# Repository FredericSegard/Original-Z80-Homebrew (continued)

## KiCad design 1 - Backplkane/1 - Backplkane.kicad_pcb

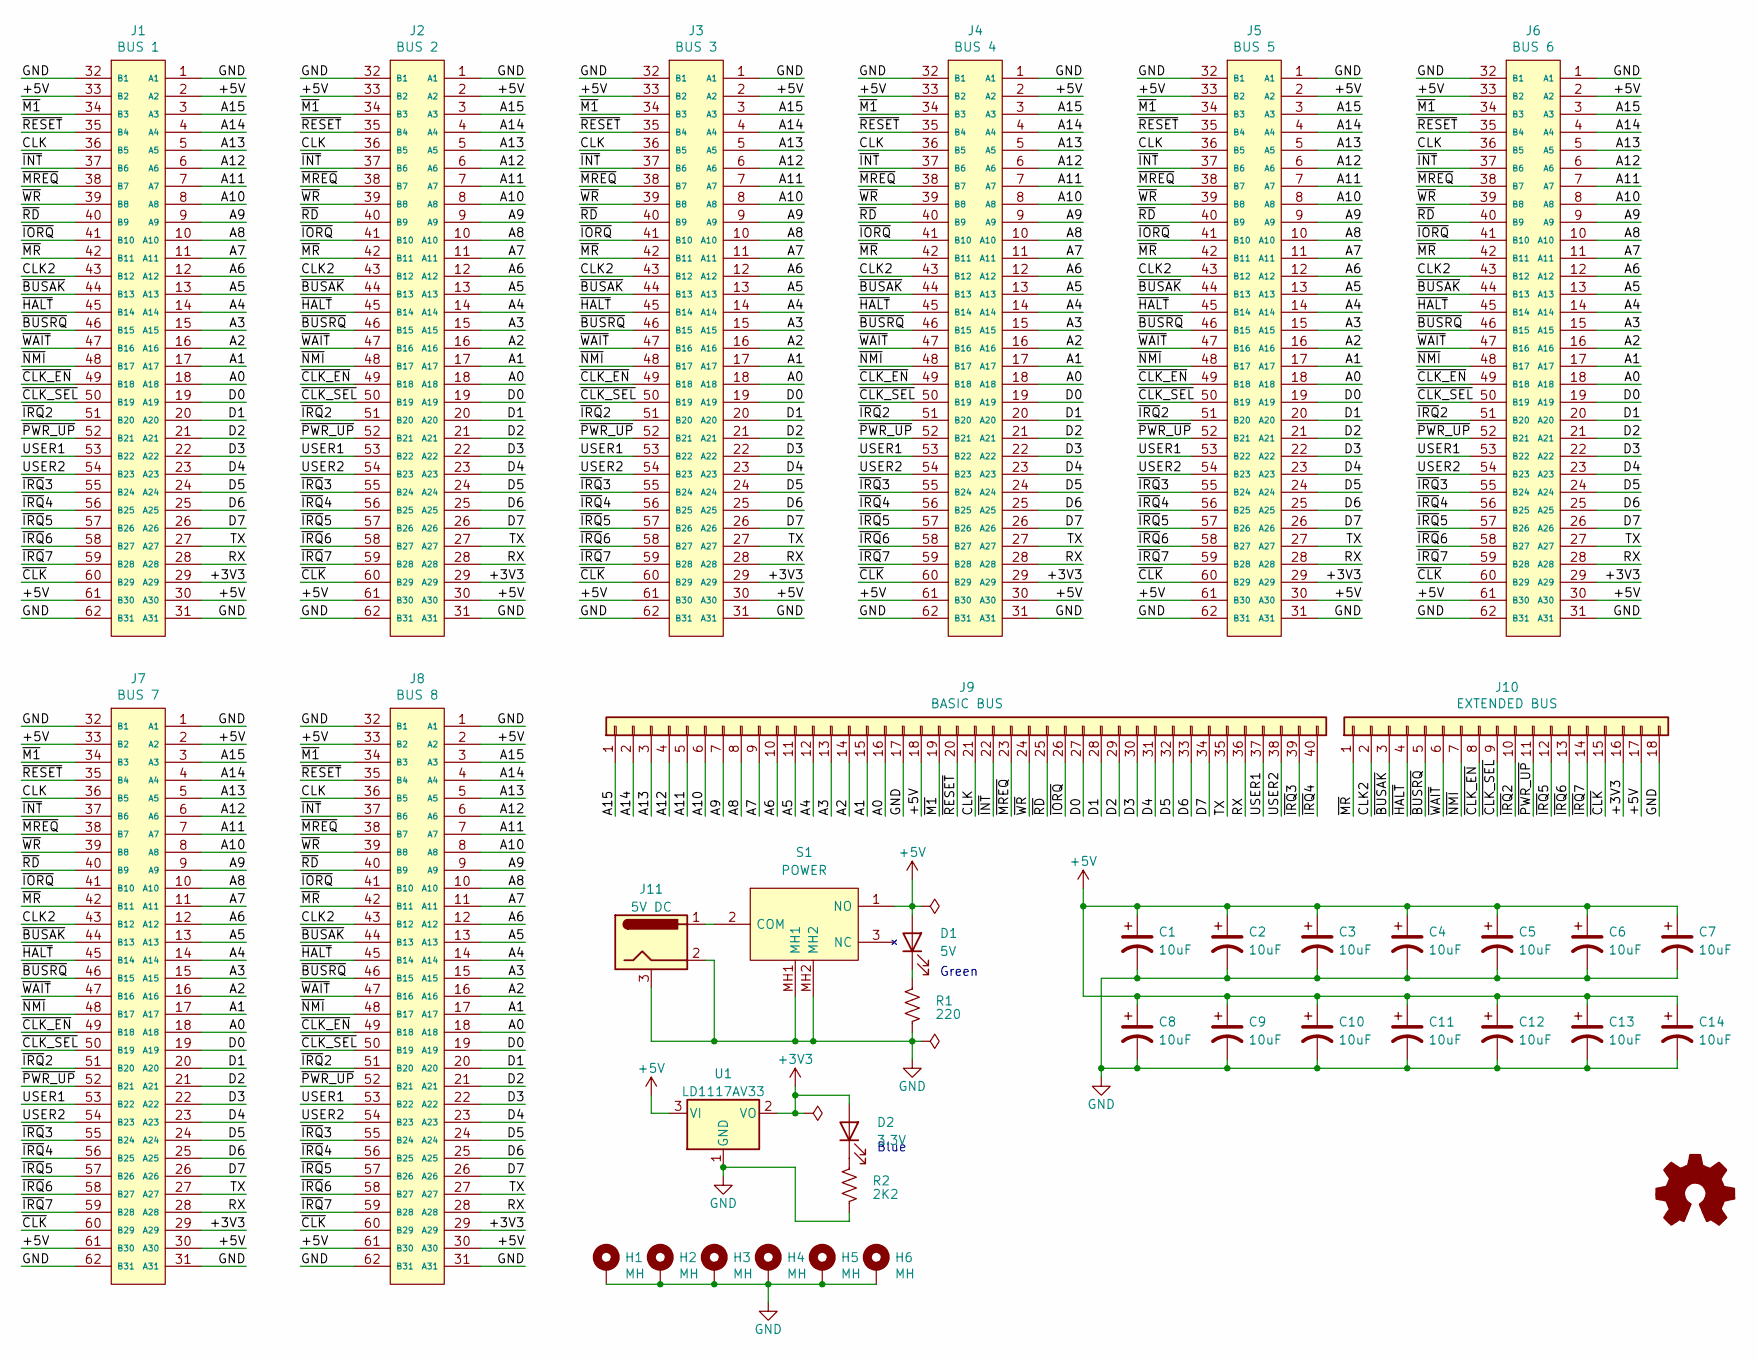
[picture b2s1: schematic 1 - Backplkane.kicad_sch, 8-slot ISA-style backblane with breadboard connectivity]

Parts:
C1, C2, C3, C4, C5, C6, C7, C8, C9, C10, C11, C12, C13, C14: 10uF; CP_Radial_D6.3mm_P2.50mm
D1: 5V; LED_D3.0mm
D2: 3.3V; LED_D3.0mm
H1, H2, H3, H4, H5, H6: MH; MountingHole_3.2mm_M3_Pad_Via
J1: BUS 1; ISA_Connector; Mouser Part Number 571-6-5530843-5
J2: BUS 2; ISA_Connector; Mouser Part Number 571-6-5530843-5
J3: BUS 3; ISA_Connector; Mouser Part Number 571-6-5530843-5
J4: BUS 4; ISA_Connector; Mouser Part Number 571-6-5530843-5
J5: BUS 5; ISA_Connector; Mouser Part Number 571-6-5530843-5
J6: BUS 6; ISA_Connector; Mouser Part Number 571-6-5530843-5
J7: BUS 7; ISA_Connector; Mouser Part Number 571-6-5530843-5
J8: BUS 8; ISA_Connector; Mouser Part Number 571-6-5530843-5
J9: BASIC BUS; PinHeader_1x40_P2.54mm_Vertical
J10: EXTENDED BUS; PinHeader_1x18_P2.54mm_Vertical
J11: 5V DC; BarrelJack_Horizontal
R1: 220; R_Axial_DIN0207_L6.3mm_D2.5mm_P10.16mm_Horizontal
R2: 2K2; R_Axial_DIN0207_L6.3mm_D2.5mm_P10.16mm_Horizontal
S1: POWER; SPDT_NKK_SWITCH_M2012S2A2W30; Manufacturer_Part_Number M2012S2A2W30; Mouser Part Number 633-M2012S2A2W30
U1: LD1117AV33; TO-126-3_Horizontal_TabDown

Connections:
+3V3: D2.2 (A), J1.29 (A29), J2.29 (A29), J3.29 (A29), J4.29 (A29), J5.29 (A29), J6.29 (A29), J7.29 (A29), J8.29 (A29), J10.16, U1.2 (VO)
+5V: C1.1, C2.1, C3.1, C4.1, C5.1, C6.1, C7.1, C8.1, C9.1, C10.1, C11.1, C12.1, C13.1, C14.1, D1.2 (A), J1.2 (A2), J1.30 (A30), J1.33 (B2), J1.61 (B30), J2.2 (A2), J2.30 (A30), J2.33 (B2), J2.61 (B30), J3.2 (A2), J3.30 (A30), J3.33 (B2), J3.61 (B30), J4.2 (A2), J4.30 (A30), J4.33 (B2), J4.61 (B30), J5.2 (A2), J5.30 (A30), J5.33 (B2), J5.61 (B30), J6.2 (A2), J6.30 (A30), J6.33 (B2), J6.61 (B30), J7.2 (A2), J7.30 (A30), J7.33 (B2), J7.61 (B30), J8.2 (A2), J8.30 (A30), J8.33 (B2), J8.61 (B30), J9.18, J10.17, S1.1 (NO), U1.3 (VI)
/A0: J1.18 (A18), J2.18 (A18), J3.18 (A18), J4.18 (A18), J5.18 (A18), J6.18 (A18), J7.18 (A18), J8.18 (A18), J9.16
/A1: J1.17 (A17), J2.17 (A17), J3.17 (A17), J4.17 (A17), J5.17 (A17), J6.17 (A17), J7.17 (A17), J8.17 (A17), J9.15
/A2: J1.16 (A16), J2.16 (A16), J3.16 (A16), J4.16 (A16), J5.16 (A16), J6.16 (A16), J7.16 (A16), J8.16 (A16), J9.14
/A3: J1.15 (A15), J2.15 (A15), J3.15 (A15), J4.15 (A15), J5.15 (A15), J6.15 (A15), J7.15 (A15), J8.15 (A15), J9.13
/A4: J1.14 (A14), J2.14 (A14), J3.14 (A14), J4.14 (A14), J5.14 (A14), J6.14 (A14), J7.14 (A14), J8.14 (A14), J9.12
/A5: J1.13 (A13), J2.13 (A13), J3.13 (A13), J4.13 (A13), J5.13 (A13), J6.13 (A13), J7.13 (A13), J8.13 (A13), J9.11
/A6: J1.12 (A12), J2.12 (A12), J3.12 (A12), J4.12 (A12), J5.12 (A12), J6.12 (A12), J7.12 (A12), J8.12 (A12), J9.10
/A7: J1.11 (A11), J2.11 (A11), J3.11 (A11), J4.11 (A11), J5.11 (A11), J6.11 (A11), J7.11 (A11), J8.11 (A11), J9.9
/A8: J1.10 (A10), J2.10 (A10), J3.10 (A10), J4.10 (A10), J5.10 (A10), J6.10 (A10), J7.10 (A10), J8.10 (A10), J9.8
/A9: J1.9 (A9), J2.9 (A9), J3.9 (A9), J4.9 (A9), J5.9 (A9), J6.9 (A9), J7.9 (A9), J8.9 (A9), J9.7
/A10: J1.8 (A8), J2.8 (A8), J3.8 (A8), J4.8 (A8), J5.8 (A8), J6.8 (A8), J7.8 (A8), J8.8 (A8), J9.6
/A11: J1.7 (A7), J2.7 (A7), J3.7 (A7), J4.7 (A7), J5.7 (A7), J6.7 (A7), J7.7 (A7), J8.7 (A7), J9.5
/A12: J1.6 (A6), J2.6 (A6), J3.6 (A6), J4.6 (A6), J5.6 (A6), J6.6 (A6), J7.6 (A6), J8.6 (A6), J9.4
/A13: J1.5 (A5), J2.5 (A5), J3.5 (A5), J4.5 (A5), J5.5 (A5), J6.5 (A5), J7.5 (A5), J8.5 (A5), J9.3
/A14: J1.4 (A4), J2.4 (A4), J3.4 (A4), J4.4 (A4), J5.4 (A4), J6.4 (A4), J7.4 (A4), J8.4 (A4), J9.2
/A15: J1.3 (A3), J2.3 (A3), J3.3 (A3), J4.3 (A3), J5.3 (A3), J6.3 (A3), J7.3 (A3), J8.3 (A3), J9.1
/CLK: J1.36 (B5), J2.36 (B5), J3.36 (B5), J4.36 (B5), J5.36 (B5), J6.36 (B5), J7.36 (B5), J8.36 (B5), J9.21
/CLK2: J1.43 (B12), J2.43 (B12), J3.43 (B12), J4.43 (B12), J5.43 (B12), J6.43 (B12), J7.43 (B12), J8.43 (B12), J10.2
/D0: J1.19 (A19), J2.19 (A19), J3.19 (A19), J4.19 (A19), J5.19 (A19), J6.19 (A19), J7.19 (A19), J8.19 (A19), J9.27
/D1: J1.20 (A20), J2.20 (A20), J3.20 (A20), J4.20 (A20), J5.20 (A20), J6.20 (A20), J7.20 (A20), J8.20 (A20), J9.28
/D2: J1.21 (A21), J2.21 (A21), J3.21 (A21), J4.21 (A21), J5.21 (A21), J6.21 (A21), J7.21 (A21), J8.21 (A21), J9.29
/D3: J1.22 (A22), J2.22 (A22), J3.22 (A22), J4.22 (A22), J5.22 (A22), J6.22 (A22), J7.22 (A22), J8.22 (A22), J9.30
/D4: J1.23 (A23), J2.23 (A23), J3.23 (A23), J4.23 (A23), J5.23 (A23), J6.23 (A23), J7.23 (A23), J8.23 (A23), J9.31
/D5: J1.24 (A24), J2.24 (A24), J3.24 (A24), J4.24 (A24), J5.24 (A24), J6.24 (A24), J7.24 (A24), J8.24 (A24), J9.32
/D6: J1.25 (A25), J2.25 (A25), J3.25 (A25), J4.25 (A25), J5.25 (A25), J6.25 (A25), J7.25 (A25), J8.25 (A25), J9.33
/D7: J1.26 (A26), J2.26 (A26), J3.26 (A26), J4.26 (A26), J5.26 (A26), J6.26 (A26), J7.26 (A26), J8.26 (A26), J9.34
/RX: J1.28 (A28), J2.28 (A28), J3.28 (A28), J4.28 (A28), J5.28 (A28), J6.28 (A28), J7.28 (A28), J8.28 (A28), J9.36
/TX: J1.27 (A27), J2.27 (A27), J3.27 (A27), J4.27 (A27), J5.27 (A27), J6.27 (A27), J7.27 (A27), J8.27 (A27), J9.35
/USER1: J1.53 (B22), J2.53 (B22), J3.53 (B22), J4.53 (B22), J5.53 (B22), J6.53 (B22), J7.53 (B22), J8.53 (B22), J9.37
/USER2: J1.54 (B23), J2.54 (B23), J3.54 (B23), J4.54 (B23), J5.54 (B23), J6.54 (B23), J7.54 (B23), J8.54 (B23), J9.38
/~BUSAK: J1.44 (B13), J2.44 (B13), J3.44 (B13), J4.44 (B13), J5.44 (B13), J6.44 (B13), J7.44 (B13), J8.44 (B13), J10.3
/~BUSRQ: J1.46 (B15), J2.46 (B15), J3.46 (B15), J4.46 (B15), J5.46 (B15), J6.46 (B15), J7.46 (B15), J8.46 (B15), J10.5
/~CLK_EN: J1.49 (B18), J2.49 (B18), J3.49 (B18), J4.49 (B18), J5.49 (B18), J6.49 (B18), J7.49 (B18), J8.49 (B18), J10.8
/~CLK_SEL: J1.50 (B19), J2.50 (B19), J3.50 (B19), J4.50 (B19), J5.50 (B19), J6.50 (B19), J7.50 (B19), J8.50 (B19), J10.9
/~CLK: J1.60 (B29), J2.60 (B29), J3.60 (B29), J4.60 (B29), J5.60 (B29), J6.60 (B29), J7.60 (B29), J8.60 (B29), J10.15
/~HALT: J1.45 (B14), J2.45 (B14), J3.45 (B14), J4.45 (B14), J5.45 (B14), J6.45 (B14), J7.45 (B14), J8.45 (B14), J10.4
/~INT: J1.37 (B6), J2.37 (B6), J3.37 (B6), J4.37 (B6), J5.37 (B6), J6.37 (B6), J7.37 (B6), J8.37 (B6), J9.22
/~IORQ: J1.41 (B10), J2.41 (B10), J3.41 (B10), J4.41 (B10), J5.41 (B10), J6.41 (B10), J7.41 (B10), J8.41 (B10), J9.26
/~IRQ2: J1.51 (B20), J2.51 (B20), J3.51 (B20), J4.51 (B20), J5.51 (B20), J6.51 (B20), J7.51 (B20), J8.51 (B20), J10.10
/~IRQ3: J1.55 (B24), J2.55 (B24), J3.55 (B24), J4.55 (B24), J5.55 (B24), J6.55 (B24), J7.55 (B24), J8.55 (B24), J9.39
/~IRQ4: J1.56 (B25), J2.56 (B25), J3.56 (B25), J4.56 (B25), J5.56 (B25), J6.56 (B25), J7.56 (B25), J8.56 (B25), J9.40
/~IRQ5: J1.57 (B26), J2.57 (B26), J3.57 (B26), J4.57 (B26), J5.57 (B26), J6.57 (B26), J7.57 (B26), J8.57 (B26), J10.12
/~IRQ6: J1.58 (B27), J2.58 (B27), J3.58 (B27), J4.58 (B27), J5.58 (B27), J6.58 (B27), J7.58 (B27), J8.58 (B27), J10.13
/~IRQ7: J1.59 (B28), J2.59 (B28), J3.59 (B28), J4.59 (B28), J5.59 (B28), J6.59 (B28), J7.59 (B28), J8.59 (B28), J10.14
/~M1: J1.34 (B3), J2.34 (B3), J3.34 (B3), J4.34 (B3), J5.34 (B3), J6.34 (B3), J7.34 (B3), J8.34 (B3), J9.19
/~MREQ: J1.38 (B7), J2.38 (B7), J3.38 (B7), J4.38 (B7), J5.38 (B7), J6.38 (B7), J7.38 (B7), J8.38 (B7), J9.23
/~MR: J1.42 (B11), J2.42 (B11), J3.42 (B11), J4.42 (B11), J5.42 (B11), J6.42 (B11), J7.42 (B11), J8.42 (B11), J10.1
/~NMI: J1.48 (B17), J2.48 (B17), J3.48 (B17), J4.48 (B17), J5.48 (B17), J6.48 (B17), J7.48 (B17), J8.48 (B17), J10.7
/~PWR_UP: J1.52 (B21), J2.52 (B21), J3.52 (B21), J4.52 (B21), J5.52 (B21), J6.52 (B21), J7.52 (B21), J8.52 (B21), J10.11
/~RD: J1.40 (B9), J2.40 (B9), J3.40 (B9), J4.40 (B9), J5.40 (B9), J6.40 (B9), J7.40 (B9), J8.40 (B9), J9.25
/~RESET: J1.35 (B4), J2.35 (B4), J3.35 (B4), J4.35 (B4), J5.35 (B4), J6.35 (B4), J7.35 (B4), J8.35 (B4), J9.20
/~WAIT: J1.47 (B16), J2.47 (B16), J3.47 (B16), J4.47 (B16), J5.47 (B16), J6.47 (B16), J7.47 (B16), J8.47 (B16), J10.6
/~WR: J1.39 (B8), J2.39 (B8), J3.39 (B8), J4.39 (B8), J5.39 (B8), J6.39 (B8), J7.39 (B8), J8.39 (B8), J9.24
GND: C1.2, C2.2, C3.2, C4.2, C5.2, C6.2, C7.2, C8.2, C9.2, C10.2, C11.2, C12.2, C13.2, C14.2, H1.1, H2.1, H3.1, H4.1, H5.1, H6.1, J1.1 (A1), J1.31 (A31), J1.32 (B1), J1.62 (B31), J2.1 (A1), J2.31 (A31), J2.32 (B1), J2.62 (B31), J3.1 (A1), J3.31 (A31), J3.32 (B1), J3.62 (B31), J4.1 (A1), J4.31 (A31), J4.32 (B1), J4.62 (B31), J5.1 (A1), J5.31 (A31), J5.32 (B1), J5.62 (B31), J6.1 (A1), J6.31 (A31), J6.32 (B1), J6.62 (B31), J7.1 (A1), J7.31 (A31), J7.32 (B1), J7.62 (B31), J8.1 (A1), J8.31 (A31), J8.32 (B1), J8.62 (B31), J9.17, J10.18, J11.2, J11.3, R1.1, R2.1, S1.MH1, S1.MH2, U1.1 (GND)
unnamed: D1.1 (K), R1.2
unnamed: D2.1 (K), R2.2
unnamed: J11.1, S1.2 (COM)

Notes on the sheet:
Blue
Green

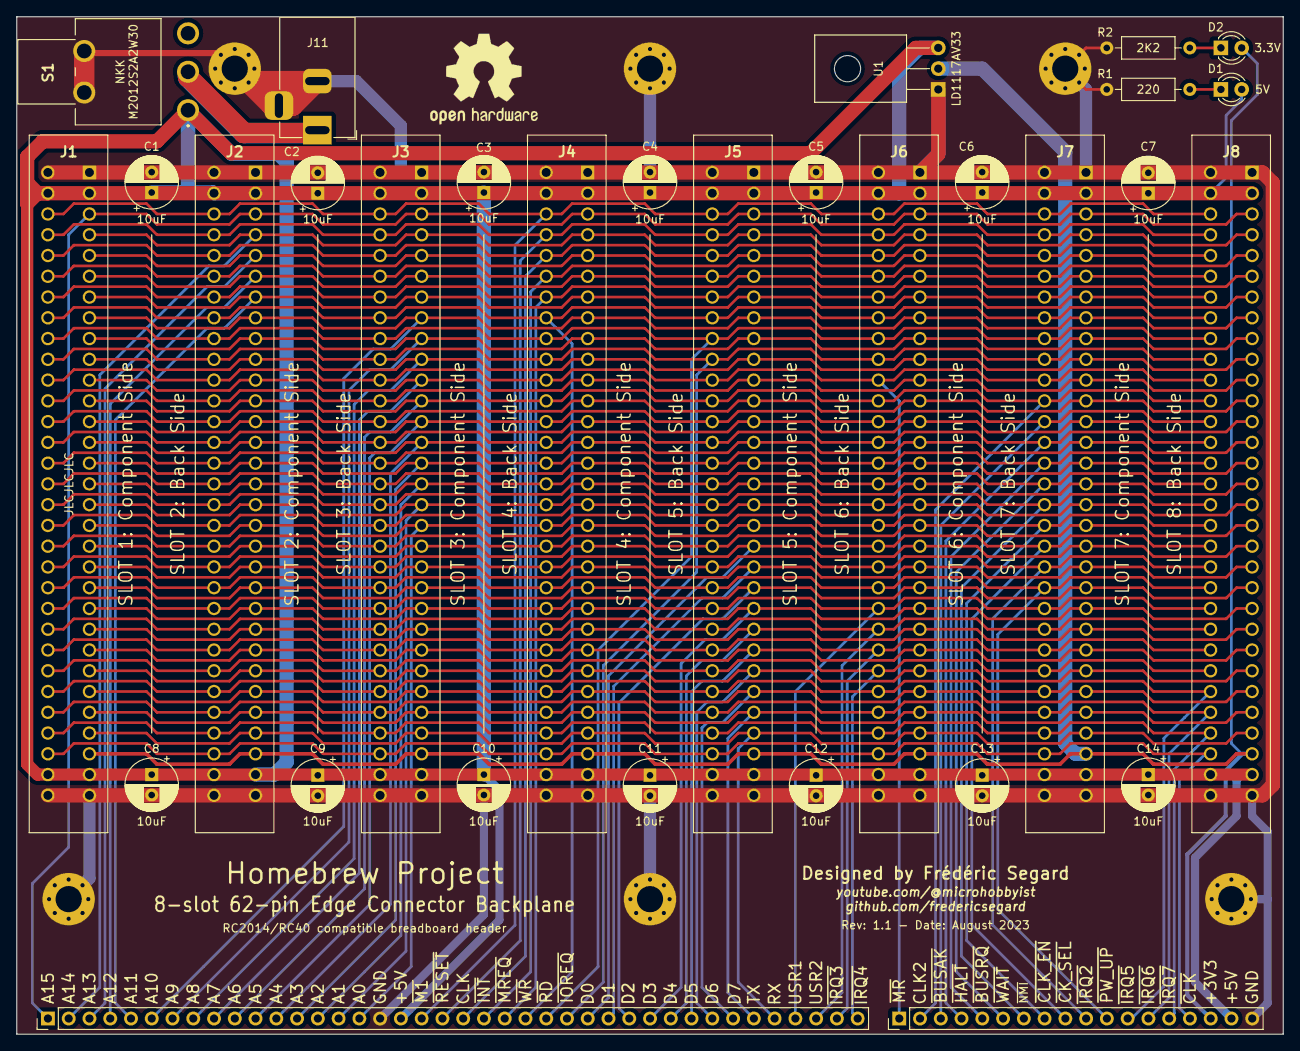
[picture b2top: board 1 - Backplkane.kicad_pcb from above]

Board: 2 copper layers, 154.9 x 124.5 mm, 37 parts (0 on the bottom side), 59 nets.

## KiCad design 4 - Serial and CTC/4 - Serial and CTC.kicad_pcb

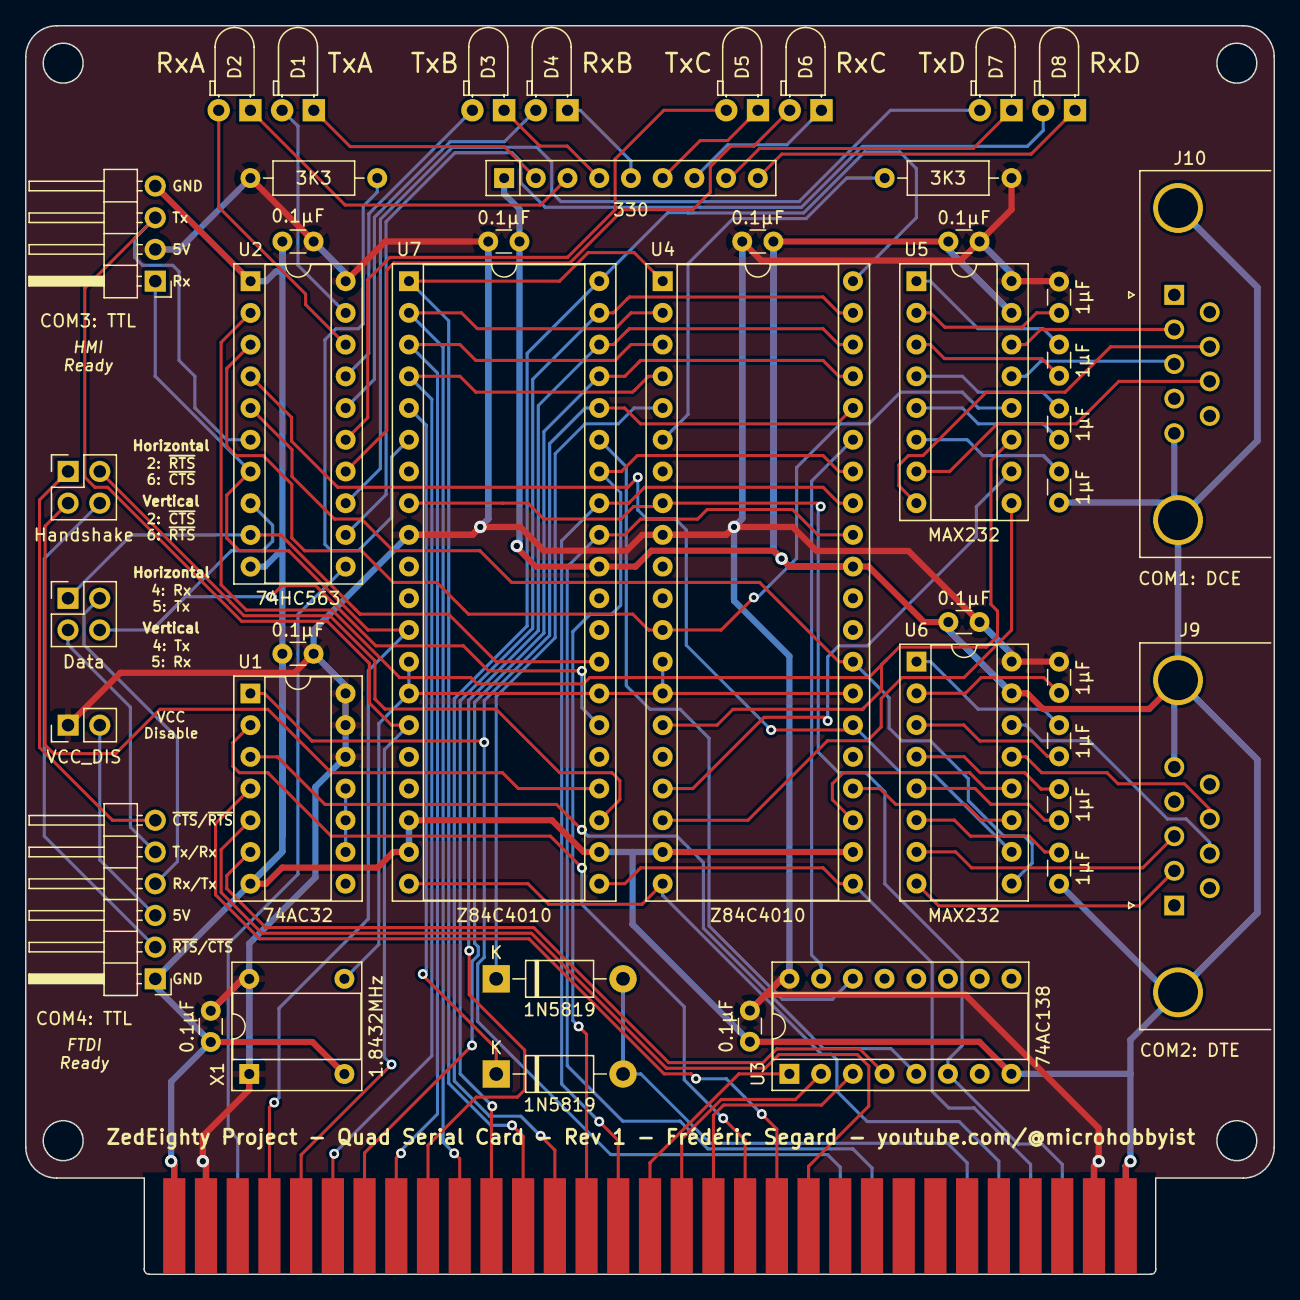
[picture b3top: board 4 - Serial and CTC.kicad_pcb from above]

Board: 2 copper layers, 100.0 x 100.0 mm, 45 parts (0 on the bottom side), 90 nets.

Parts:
C1, C2, C3, C4, C5, C6, C7, C16: 0.1µF; C_Disc_D3.0mm_W1.6mm_P2.50mm
C8, C9, C10, C11, C12, C13, C14, C15: 1µF; C_Disc_D3.0mm_W1.6mm_P2.50mm
D1: TxA; LED_D3.0mm_Horizontal_O1.27mm_Z2.0mm_Clear
D2: RxA; LED_D3.0mm_Horizontal_O1.27mm_Z2.0mm_Clear
D3: TxB; LED_D3.0mm_Horizontal_O1.27mm_Z2.0mm_Clear
D4: RxB; LED_D3.0mm_Horizontal_O1.27mm_Z2.0mm_Clear
D5: TxC; LED_D3.0mm_Horizontal_O1.27mm_Z2.0mm_Clear
D6: RxC; LED_D3.0mm_Horizontal_O1.27mm_Z2.0mm_Clear
D7: TxD; LED_D3.0mm_Horizontal_O1.27mm_Z2.0mm_Clear
D8: RxD; LED_D3.0mm_Horizontal_O1.27mm_Z2.0mm_Clear
D9, D10: 1N5819; D_DO-41_SOD81_P10.16mm_Horizontal
J1: EDGE; BUS_XT
J4: Handshake; PinHeader_2x02_P2.54mm_Vertical
J5: Data; PinHeader_2x02_P2.54mm_Vertical
J6: COM3: TTL; PinHeader_1x04_P2.54mm_Horizontal
J7: VCC_DIS; PinHeader_1x02_P2.54mm_Vertical
J8: COM4: TTL; PinHeader_1x06_P2.54mm_Horizontal
J9: COM2: DTE; DSUB-9_Male_Horizontal_P2.77x2.84mm_EdgePinOffset4.94mm_Hou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
J10: COM1: DCE; DSUB-9_Female_Horizontal_P2.77x2.84mm_EdgePinOffset4.94mm_H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
R1, R2: 3K3; R_Axial_DIN0207_L6.3mm_D2.5mm_P10.16mm_Horizontal
RN1: 330; R_Array_SIP9
U1: 74AC32; DIP-14_W7.62mm_Socket
U2: 74HC563; DIP-20_W7.62mm_Socket
U3: 74AC138; DIP-16_W7.62mm_Socket
U4, U7: Z84C4010; DIP-40_W15.24mm_Socket
U5, U6: MAX232; DIP-16_W7.62mm_Socket
X1: 1.8432MHz; DIP-8-4_W7.62mm_Oscillator_Socket

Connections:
+5V: C1.1, C2.1, C3.1, C4.1, C5.1, C6.1, C7.1, C12.1, C14.1, C16.1, J1.2 (A2), J1.30 (A30), J1.33 (B2), J1.61 (B30), J6.2, J7.1, R1.1, R2.1, U1.12, U1.13, U1.14 (VCC), U2.20 (VCC), U3.16 (VCC), U4.9 (VCC), U5.16 (VCC), U6.16 (VCC), U7.9 (VCC), X1.1 (EN), X1.8 (Vcc)
/A0: J1.18 (A18), U4.34 (B/~A), U7.34 (B/~A)
/A1: J1.17 (A17), U4.33 (C/~D), U7.33 (C/~D)
/A2: J1.16 (A16), U3.1 (A0)
/A3: J1.15 (A15), U3.2 (A1)
/A4: J1.14 (A14), U3.3 (A2)
/A5: J1.13 (A13), U1.2
/A6: J1.12 (A12), U1.4
/A7: J1.11 (A11), U1.5
/CLK: J1.36 (B5), U4.20 (CLK), U7.20 (CLK)
/COM 1 and 2 (RS-232)/~CTSA: U4.18 (~CTSA), U5.9 (R1out)
/COM 1 and 2 (RS-232)/~CTSB: U4.23 (~CTSB), U6.12 (R1out)
/COM 1 and 2 (RS-232)/~RTSA: U4.17 (~RTSA), U5.10 (T2in)
/COM 1 and 2 (RS-232)/~RTSB: U4.24 (~RTSB), U6.11 (T1in)
/COM 3 and 4 (TTL)/~CTSD: J4.2, U7.23 (~CTSB)
/COM 3 and 4 (TTL)/~RTSD: J4.3, U7.24 (~RTSB)
/D0: J1.19 (A19), U4.40 (D0), U7.40 (D0)
/D1: J1.20 (A20), U4.1 (D1), U7.1 (D1)
/D2: J1.21 (A21), U4.39 (D2), U7.39 (D2)
/D3: J1.22 (A22), U4.2 (D3), U7.2 (D3)
/D4: J1.23 (A23), U4.38 (D4), U7.38 (D4)
/D5: J1.24 (A24), U4.3 (D5), U7.3 (D5)
/D6: J1.25 (A25), U4.37 (D6), U7.37 (D6)
/D7: J1.26 (A26), U4.4 (D7), U7.4 (D7)
/RxA: U2.3 (D1), U4.12 (RxDA), U5.12 (R1out)
/RxB: U2.5 (D3), U4.28 (RxDB), U6.9 (R1out)
/RxC: J1.28 (A28), J6.1, U2.7 (D5), U7.12 (RxDA)
/RxD: J5.1, U2.9 (D7), U7.28 (RxDB)
/SIOCLK: U4.13 (~RxCA), U4.14 (~TxCA), U4.27 (~RxTxCB), U7.13 (~RxCA), U7.14 (~TxCA), U7.27 (~RxTxCB), X1.5 (OUT)
/TxA: U2.2 (D0), U4.15 (TxDA), U5.11 (T1in)
/TxB: U2.4 (D2), U4.26 (TxDB), U6.10 (T2in)
/TxC: J1.27 (A27), J6.3, U2.6 (D4), U7.15 (TxDA)
/TxD: J5.4, U2.8 (D6), U7.26 (TxDB)
/~CLK: J1.60 (B29), U2.11 (LE)
/~INT: D9.2 (A), D10.2 (A), J1.37 (B6)
/~IORQ: J1.41 (B10), U1.1, U4.36 (~IORQ), U7.36 (~IORQ)
/~M1: J1.34 (B3), U3.6 (E3), U4.8 (~M1), U7.8 (~M1)
/~RD: J1.40 (B9), U4.32 (~RD), U7.32 (~RD)
/~RESET: J1.35 (B4), U4.21 (~RST), U7.21 (~RST)
/~SIO1_CS: U3.15 (O0), U4.35 (~CE)
/~SIO2_CS: U3.14 (O1), U7.35 (~CE)
GND: C1.2, C2.2, C3.2, C4.2, C5.2, C6.2, C7.2, C9.2, C11.2, C16.2, J1.1 (A1), J1.31 (A31), J1.32 (B1), J1.62 (B31), J6.4, J8.1, J9.0 (PAD), J9.5, J10.0 (PAD), J10.5, RN1.1 (common), U1.7 (GND), U2.1 (OE), U2.10 (GND), U3.8 (GND), U4.19 (~DCDA), U4.22 (~DCDB), U4.31 (GND), U5.15 (GND), U6.15 (GND), U7.18 (~CTSA), U7.19 (~DCDA), U7.22 (~DCDB), U7.31 (GND), X1.4 (GND)
unnamed: D1.2 (A), U2.19 (Q0)
unnamed: D1.1 (K), RN1.2 (R1)
unnamed: D2.2 (A), U2.18 (Q1)
unnamed: D2.1 (K), RN1.3 (R2)
unnamed: D3.2 (A), U2.17 (Q2)
unnamed: D3.1 (K), RN1.4 (R3)
unnamed: D4.2 (A), U2.16 (Q3)
unnamed: D4.1 (K), RN1.5 (R4)
unnamed: D5.2 (A), U2.15 (Q4)
unnamed: D5.1 (K), RN1.6 (R5)
unnamed: D6.2 (A), U2.14 (Q5)
unnamed: D6.1 (K), RN1.7 (R6)
unnamed: D7.2 (A), U2.13 (Q6)
unnamed: D7.1 (K), RN1.8 (R7)
unnamed: D8.2 (A), U2.12 (Q7)
unnamed: D8.1 (K), RN1.9 (R8)
unnamed: D9.1 (K), U4.5 (~INT)
unnamed: D10.1 (K), U7.5 (~INT)
unnamed: J4.1, J8.6
unnamed: J4.4, J8.2
unnamed: J5.2, J8.4
unnamed: J5.3, J8.5
unnamed: J7.2, J8.3
unnamed: U1.9, U1.10, U1.11
unnamed: U1.6, U3.4 (E1)
unnamed: U1.3, U3.5 (E2)
unnamed: R1.2, U4.6 (IEI)
unnamed: C8.1, U5.1 (C1+)
unnamed: C8.2, U5.3 (C1-)
unnamed: C13.1, U5.4 (C2+)
unnamed: C13.2, U5.5 (C2-)
unnamed: J10.3, U5.13 (R1in)
unnamed: J10.7, U5.8 (R2in)
unnamed: J10.2, U5.14 (T1out)
unnamed: J10.8, U5.7 (T2out)
unnamed: C12.2, U5.2 (VS+)
unnamed: C9.1, U5.6 (VS-)
unnamed: C10.1, U6.1 (C1+)
unnamed: C10.2, U6.3 (C1-)
unnamed: C15.1, U6.4 (C2+)
unnamed: C15.2, U6.5 (C2-)
unnamed: J9.8, U6.13 (R1in)
unnamed: J9.2, U6.8 (R2in)
unnamed: J9.7, U6.14 (T1out)
unnamed: J9.3, U6.7 (T2out)
unnamed: C14.2, U6.2 (VS+)
unnamed: C11.1, U6.6 (VS-)
unnamed: R2.2, U7.6 (IEI)

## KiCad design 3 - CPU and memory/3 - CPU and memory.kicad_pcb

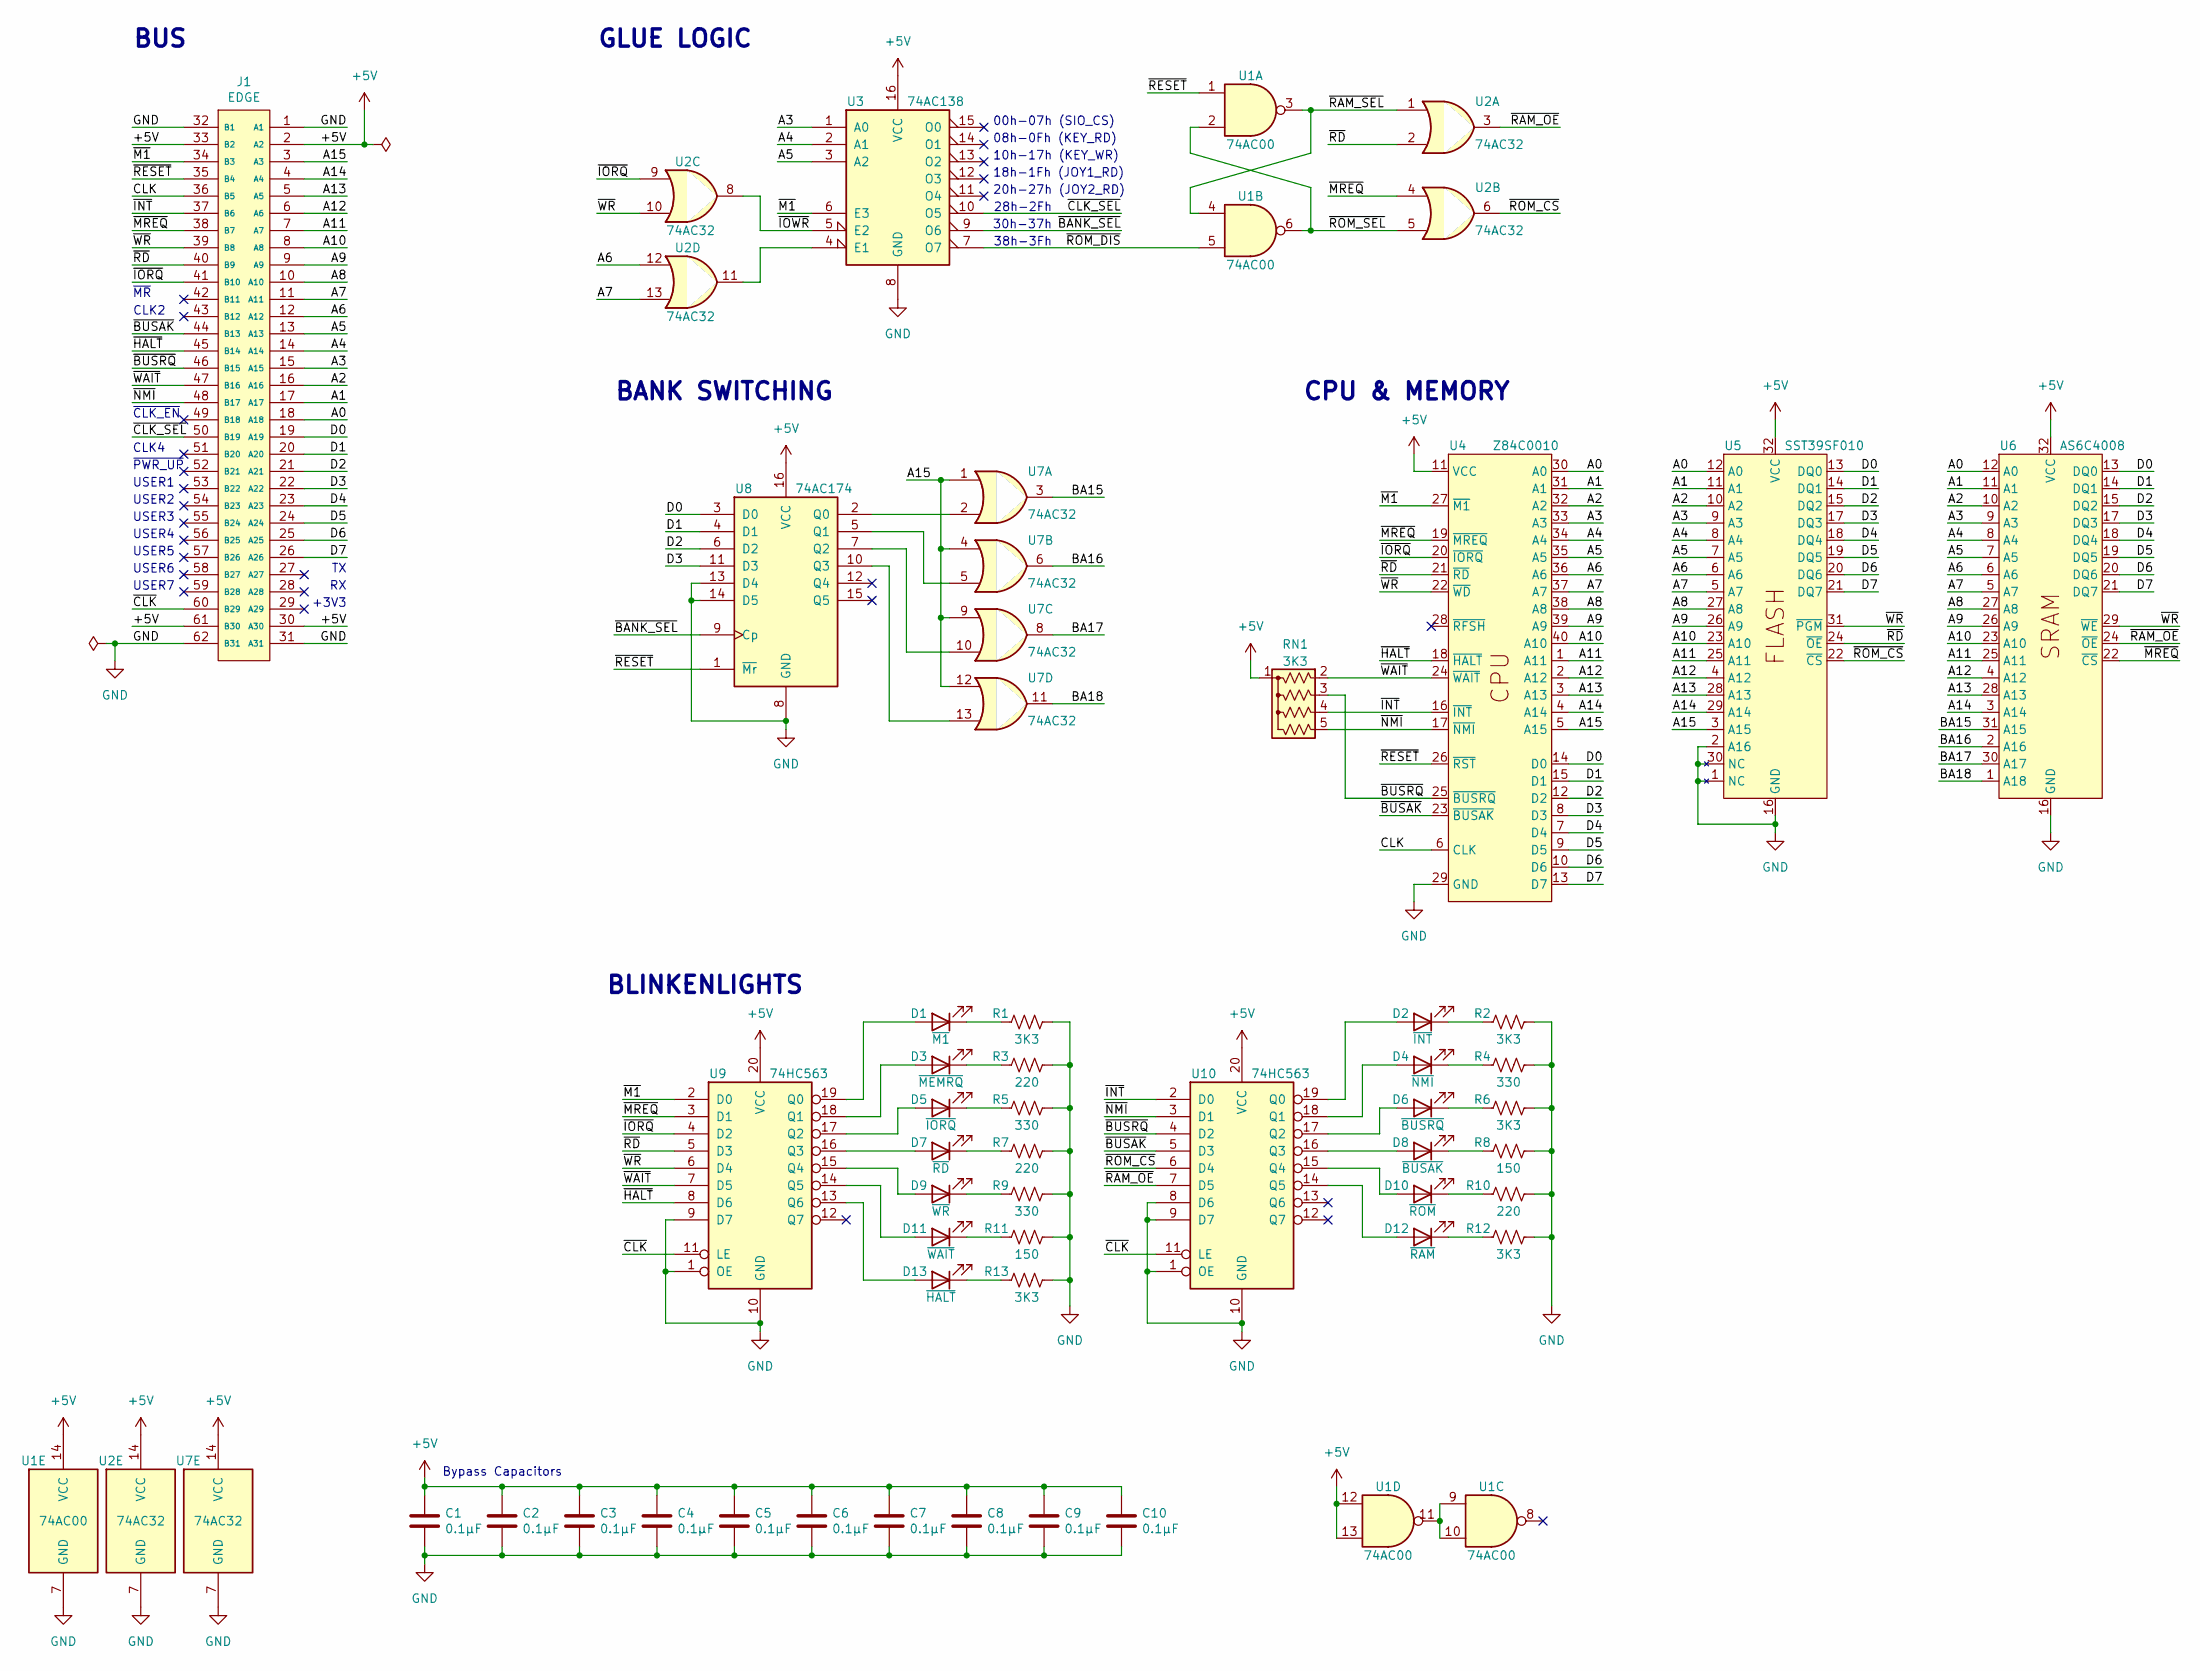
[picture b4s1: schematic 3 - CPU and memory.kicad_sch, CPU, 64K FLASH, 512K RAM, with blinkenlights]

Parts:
C1, C2, C3, C4, C5, C6, C7, C8, C9, C10: 0.1µF; C_Disc_D3.0mm_W1.6mm_P2.50mm
D1: ~{M1}; LED_D3.0mm_Horizontal_O1.27mm_Z2.0mm_Clear
D2: ~{INT}; LED_D3.0mm_Horizontal_O1.27mm_Z2.0mm_Clear
D3: ~{MEMRQ}; LED_D3.0mm_Horizontal_O1.27mm_Z2.0mm_Clear
D4: ~{NMI}; LED_D3.0mm_Horizontal_O1.27mm_Z2.0mm_Clear
D5: ~{IORQ}; LED_D3.0mm_Horizontal_O1.27mm_Z2.0mm_Clear
D6: ~{BUSRQ}; LED_D3.0mm_Horizontal_O1.27mm_Z2.0mm_Clear
D7: ~{RD}; LED_D3.0mm_Horizontal_O1.27mm_Z2.0mm_Clear
D8: ~{BUSAK}; LED_D3.0mm_Horizontal_O1.27mm_Z2.0mm_Clear
D9: ~{WR}; LED_D3.0mm_Horizontal_O1.27mm_Z2.0mm_Clear
D10: ~{ROM}; LED_D3.0mm_Horizontal_O1.27mm_Z2.0mm_Clear
D11: ~{WAIT}; LED_D3.0mm_Horizontal_O1.27mm_Z2.0mm_Clear
D12: ~{RAM}; LED_D3.0mm_Horizontal_O1.27mm_Z2.0mm_Clear
D13: ~{HALT}; LED_D3.0mm_Horizontal_O1.27mm_Z2.0mm_Clear
J1: EDGE; BUS_XT_Proto; Mouser Part Number 571-6-5530843-5
R1, R2, R6, R12, R13: 3K3; R_Axial_DIN0207_L6.3mm_D2.5mm_P10.16mm_Horizontal
R3, R7, R10: 220; R_Axial_DIN0207_L6.3mm_D2.5mm_P10.16mm_Horizontal
R4, R5, R9: 330; R_Axial_DIN0207_L6.3mm_D2.5mm_P10.16mm_Horizontal
R8, R11: 150; R_Axial_DIN0207_L6.3mm_D2.5mm_P10.16mm_Horizontal
RN1: 3K3; R_Array_SIP5
U1: 74AC00; DIP-14_W7.62mm_Socket
U2, U7: 74AC32; DIP-14_W7.62mm_Socket
U3: 74AC138; DIP-16_W7.62mm_Socket
U4: Z84C0010; DIP-40_W15.24mm_Socket
U5: SST39SF010; DIP-32_W15.24mm
U6: AS6C4008; DIP-32_W15.24mm
U8: 74AC174; DIP-16_W7.62mm_Socket
U9, U10: 74HC563; DIP-20_W7.62mm_Socket

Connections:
+5V: C1.1, C2.1, C3.1, C4.1, C5.1, C6.1, C7.1, C8.1, C9.1, C10.1, J1.2 (A2), J1.30 (A30), J1.33 (B2), J1.61 (B30), RN1.1 (common), U1.12, U1.13, U1.14 (VCC), U2.14 (VCC), U3.16 (VCC), U4.11 (VCC), U5.32 (VCC), U6.32 (VCC), U7.14 (VCC), U8.16 (VCC), U9.20 (VCC), U10.20 (VCC)
/A0: J1.18 (A18), U4.30 (A0), U5.12 (A0), U6.12 (A0)
/A1: J1.17 (A17), U4.31 (A1), U5.11 (A1), U6.11 (A1)
/A2: J1.16 (A16), U4.32 (A2), U5.10 (A2), U6.10 (A2)
/A3: J1.15 (A15), U3.1 (A0), U4.33 (A3), U5.9 (A3), U6.9 (A3)
/A4: J1.14 (A14), U3.2 (A1), U4.34 (A4), U5.8 (A4), U6.8 (A4)
/A5: J1.13 (A13), U3.3 (A2), U4.35 (A5), U5.7 (A5), U6.7 (A5)
/A6: J1.12 (A12), U2.12, U4.36 (A6), U5.6 (A6), U6.6 (A6)
/A7: J1.11 (A11), U2.13, U4.37 (A7), U5.5 (A7), U6.5 (A7)
/A8: J1.10 (A10), U4.38 (A8), U5.27 (A8), U6.27 (A8)
/A9: J1.9 (A9), U4.39 (A9), U5.26 (A9), U6.26 (A9)
/A10: J1.8 (A8), U4.40 (A10), U5.23 (A10), U6.23 (A10)
/A11: J1.7 (A7), U4.1 (A11), U5.25 (A11), U6.25 (A11)
/A12: J1.6 (A6), U4.2 (A12), U5.4 (A12), U6.4 (A12)
/A13: J1.5 (A5), U4.3 (A13), U5.28 (A13), U6.28 (A13)
/A14: J1.4 (A4), U4.4 (A14), U5.29 (A14), U6.3 (A14)
/A15: J1.3 (A3), U4.5 (A15), U5.3 (A15), U7.1, U7.4, U7.9, U7.12
/BA15: U6.31 (A15), U7.3
/BA16: U6.2 (A16), U7.6
/BA17: U6.30 (A17), U7.8
/BA18: U6.1 (A18), U7.11
/CLK: J1.36 (B5), U4.6 (CLK)
/D0: J1.19 (A19), U4.14 (D0), U5.13 (DQ0), U6.13 (DQ0), U8.3 (D0)
/D1: J1.20 (A20), U4.15 (D1), U5.14 (DQ1), U6.14 (DQ1), U8.4 (D1)
/D2: J1.21 (A21), U4.12 (D2), U5.15 (DQ2), U6.15 (DQ2), U8.6 (D2)
/D3: J1.22 (A22), U4.8 (D3), U5.17 (DQ3), U6.17 (DQ3), U8.11 (D3)
/D4: J1.23 (A23), U4.7 (D4), U5.18 (DQ4), U6.18 (DQ4)
/D5: J1.24 (A24), U4.9 (D5), U5.19 (DQ5), U6.19 (DQ5)
/D6: J1.25 (A25), U4.10 (D6), U5.20 (DQ6), U6.20 (DQ6)
/D7: J1.26 (A26), U4.13 (D7), U5.21 (DQ7), U6.21 (DQ7)
/~BANK_SEL: U3.9 (O6), U8.9 (Cp)
/~BUSAK: J1.44 (B13), U4.23 (~BUSAK), U10.5 (D3)
/~BUSRQ: J1.46 (B15), RN1.3 (R2), U4.25 (~BUSRQ), U10.4 (D2)
/~CLK_SEL: J1.50 (B19), U3.10 (O5)
/~CLK: J1.60 (B29), U9.11 (LE), U10.11 (LE)
/~HALT: J1.45 (B14), U4.18 (~HALT), U9.8 (D6)
/~INT: J1.37 (B6), RN1.4 (R3), U4.16 (~INT), U10.2 (D0)
/~IORQ: J1.41 (B10), U2.9, U4.20 (~IORQ), U9.4 (D2)
/~IOWR: U2.8, U3.5 (E2)
/~M1: J1.34 (B3), U3.6 (E3), U4.27 (~M1), U9.2 (D0)
/~MREQ: J1.38 (B7), U2.4, U4.19 (~MREQ), U6.22 (~CS), U9.3 (D1)
/~NMI: J1.48 (B17), RN1.5 (R4), U4.17 (~NMI), U10.3 (D1)
/~RAM_OE: U2.3, U6.24 (~OE), U10.7 (D5)
/~RAM_SEL: U1.3, U1.4, U2.1
/~RD: J1.40 (B9), U2.2, U4.21 (~RD), U5.24 (~OE), U9.5 (D3)
/~RESET: J1.35 (B4), U1.1, U4.26 (~RST), U8.1 (~Mr)
/~ROM_CS: U2.6, U5.22 (~CS), U10.6 (D4)
/~ROM_DIS: U1.5, U3.7 (O7)
/~ROM_SEL: U1.2, U1.6, U2.5
/~WAIT: J1.47 (B16), RN1.2 (R1), U4.24 (~WAIT), U9.7 (D5)
/~WR: J1.39 (B8), U2.10, U4.22 (~WD), U5.31 (~PGM), U6.29 (~WE), U9.6 (D4)
GND: C1.2, C2.2, C3.2, C4.2, C5.2, C6.2, C7.2, C8.2, C9.2, C10.2, J1.1 (A1), J1.31 (A31), J1.32 (B1), J1.62 (B31), R1.2, R2.2, R3.2, R4.2, R5.2, R6.2, R7.2, R8.2, R9.2, R10.2, R11.2, R12.2, R13.2, U1.7 (GND), U2.7 (GND), U3.8 (GND), U4.29 (GND), U5.1 (NC), U5.2 (A16), U5.16 (GND), U5.30 (NC), U6.16 (GND), U7.7 (GND), U8.8 (GND), U8.13 (D4), U8.14 (D5), U9.1 (OE), U9.9 (D7), U9.10 (GND), U10.1 (OE), U10.8 (D6), U10.9 (D7), U10.10 (GND)
unnamed: D1.2 (A), U9.19 (Q0)
unnamed: D1.1 (K), R1.1
unnamed: D2.2 (A), U10.19 (Q0)
unnamed: D2.1 (K), R2.1
unnamed: D3.2 (A), U9.18 (Q1)
unnamed: D3.1 (K), R3.1
unnamed: D4.2 (A), U10.18 (Q1)
unnamed: D4.1 (K), R4.1
unnamed: D5.2 (A), U9.17 (Q2)
unnamed: D5.1 (K), R5.1
unnamed: D6.2 (A), U10.17 (Q2)
unnamed: D6.1 (K), R6.1
unnamed: D7.2 (A), U9.16 (Q3)
unnamed: D7.1 (K), R7.1
unnamed: D8.2 (A), U10.16 (Q3)
unnamed: D8.1 (K), R8.1
unnamed: D9.2 (A), U9.15 (Q4)
unnamed: D9.1 (K), R9.1
unnamed: D10.2 (A), U10.15 (Q4)
unnamed: D10.1 (K), R10.1
unnamed: D11.2 (A), U9.14 (Q5)
unnamed: D11.1 (K), R11.1
unnamed: D12.2 (A), U10.14 (Q5)
unnamed: D12.1 (K), R12.1
unnamed: D13.2 (A), U9.13 (Q6)
unnamed: D13.1 (K), R13.1
unnamed: U1.9, U1.10, U1.11
unnamed: U2.11, U3.4 (E1)
unnamed: U7.2, U8.2 (Q0)
unnamed: U7.5, U8.5 (Q1)
unnamed: U7.10, U8.7 (Q2)
unnamed: U7.13, U8.10 (Q3)

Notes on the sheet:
08h-0Fh (KEY_RD)
~{CLK_EN}
38h-3Fh
USER1
GLUE LOGIC
00h-07h (SIO_CS)
BLINKENLIGHTS
BUS
18h-1Fh (JOY1_RD)
CPU & MEMORY
CLK2
CLK4
+3V3
USER5
USER3
USER2
30h-37h
10h-17h (KEY_WR)
USER4
20h-27h (JOY2_RD)
BANK SWITCHING
Bypass Capacitors
28h-2Fh
USER6
~{MR}
USER7
~{PWR_UP}

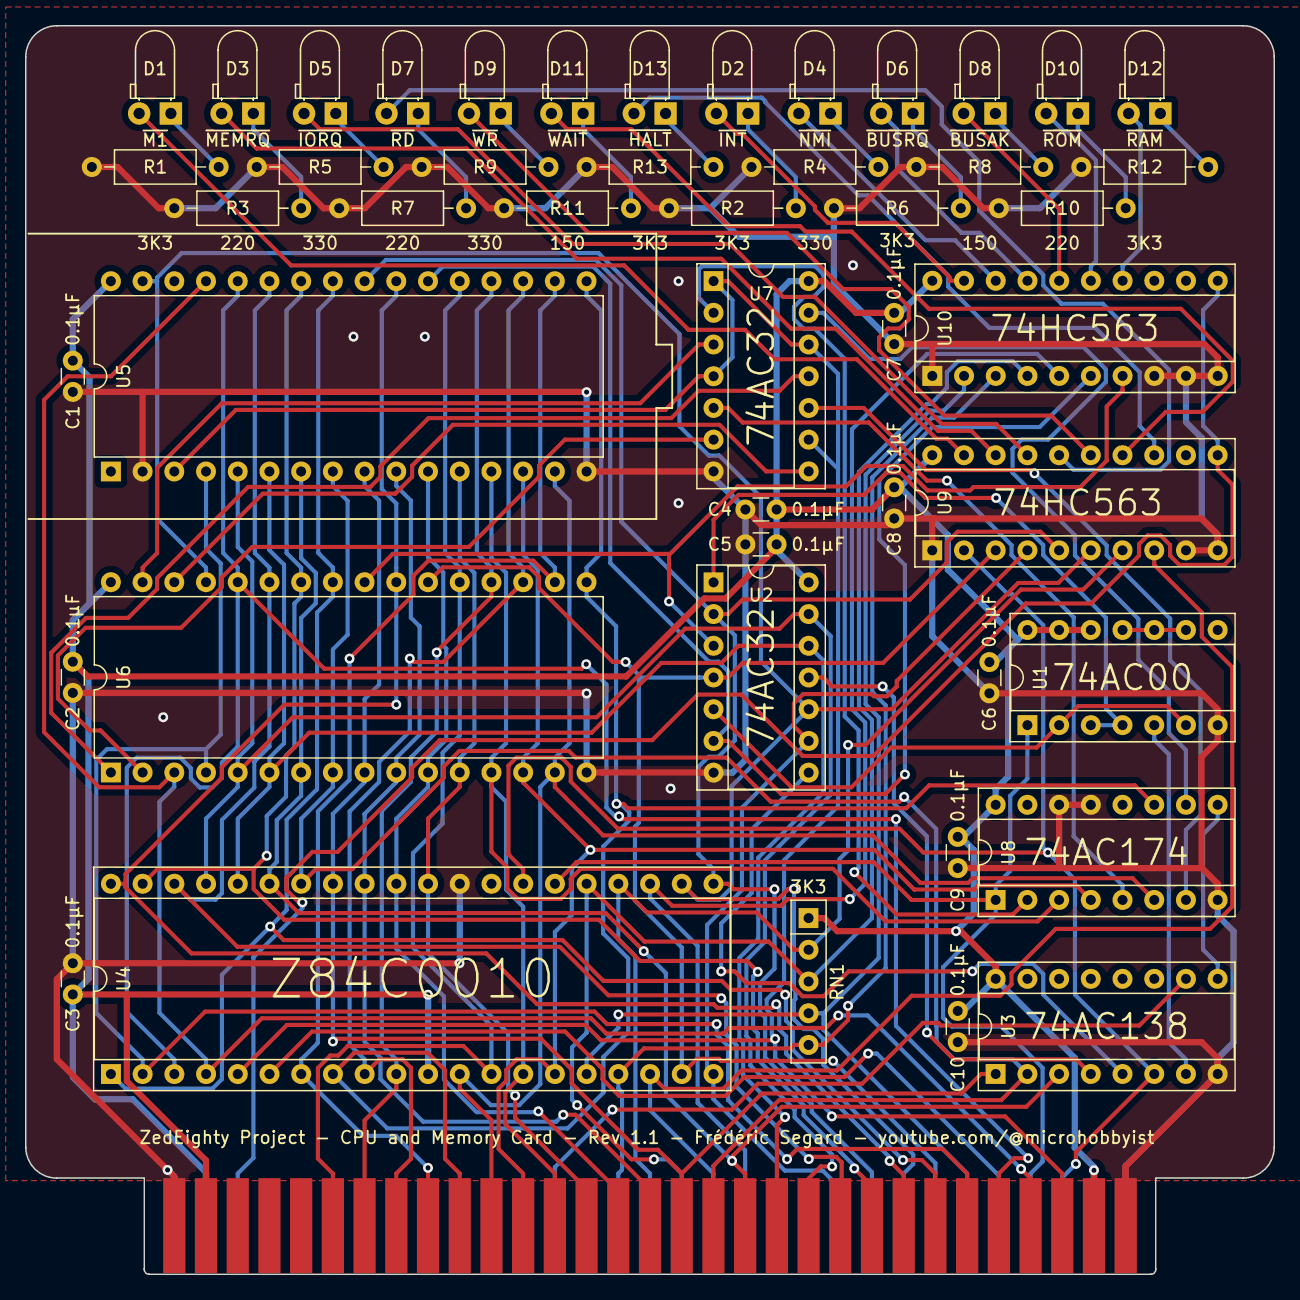
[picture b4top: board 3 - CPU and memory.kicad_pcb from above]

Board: 2 copper layers, 100.0 x 100.0 mm, 48 parts (0 on the bottom side), 84 nets.
